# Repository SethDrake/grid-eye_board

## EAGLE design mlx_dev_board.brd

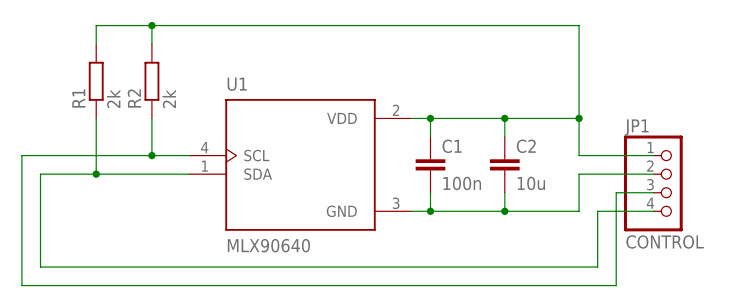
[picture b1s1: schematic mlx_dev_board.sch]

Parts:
C1: 100n; C0805
C2: 10u; C0805
JP1: CONTROL; 1X04
R1, R2: 2k; R0805
U1: MLX90640; TO292P945H1165-4

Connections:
GND: C1.2, C2.2, JP1.2, U1.3 (GND)
SCL: JP1.3, R2.1, U1.4 (SCL)
SDA: JP1.4, R1.1, U1.1 (SDA)
VDD: C1.1, C2.1, JP1.1, R1.2, R2.2, U1.2 (VDD)

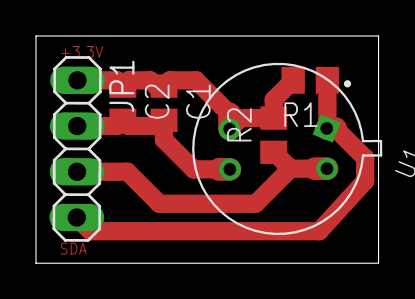
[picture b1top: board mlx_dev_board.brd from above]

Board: 2 copper layers, 19.0 x 12.6 mm, 6 parts (0 on the bottom side), 4 nets.

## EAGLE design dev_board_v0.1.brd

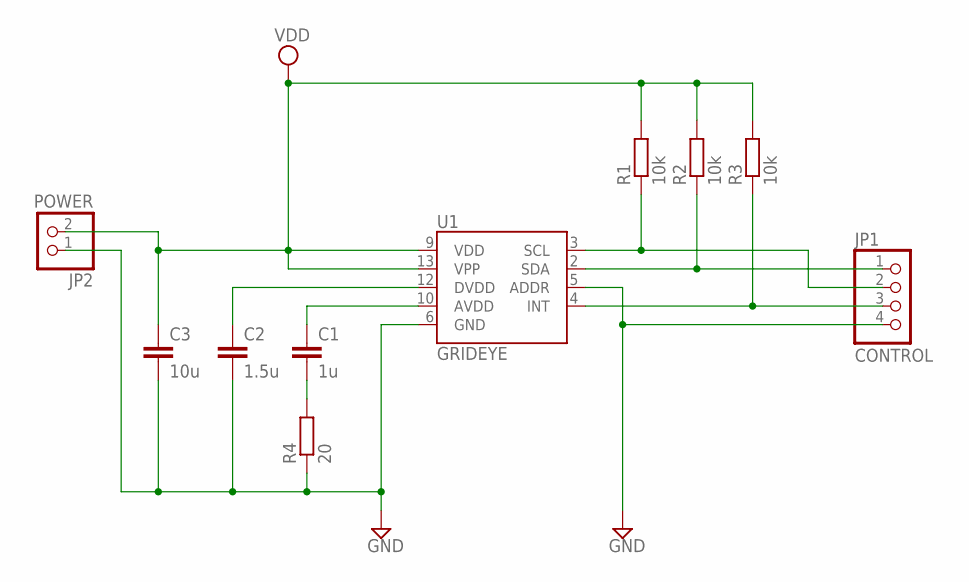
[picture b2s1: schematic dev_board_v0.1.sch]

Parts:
C1: 1u; C0805
C2: 1.5u; C0805
C3: 10u; C0805
JP1: CONTROL; 1X04
JP2: POWER; 1X02
R1, R2, R3: 10k; R0805
R4: 20; R0805
U1: GRIDEYE; GRIDEYE-AMG88

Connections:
AVDD: C1.1, U1.10 (AVDD)
DVDD: C2.1, U1.12 (DVDD)
GND: C2.2, C3.2, JP1.4, JP2.1, R4.1, U1.5 (ADDR), U1.6 (GND)
INT: JP1.3, R3.1, U1.4 (INT)
unnamed: C1.2, R4.2
SCL: JP1.2, R1.1, U1.3 (SCL)
SDA: JP1.1, R2.1, U1.2 (SDA)
VDD: C3.1, JP2.2, R1.2, R2.2, R3.2, U1.9 (VDD), U1.13 (VPP)

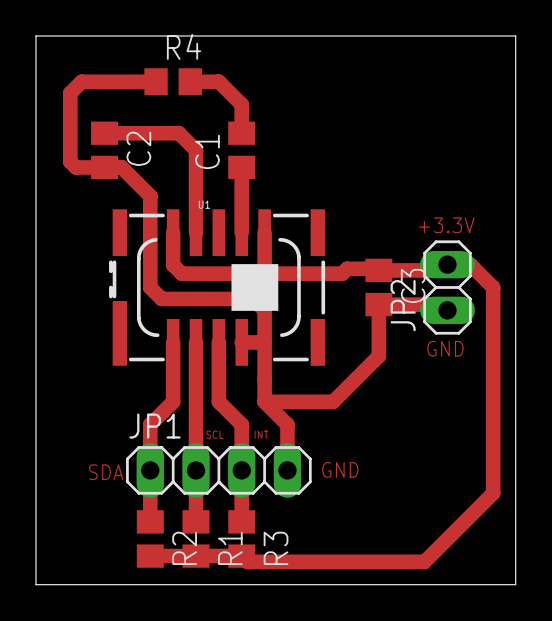
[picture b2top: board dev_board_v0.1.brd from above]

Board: 2 copper layers, 26.6 x 30.5 mm, 10 parts (0 on the bottom side), 8 nets.

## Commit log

2018-10-09 basic scheme v0.1
2018-10-09 board v0.1
2018-10-10 firmware for STM32F429-Discovery
2018-10-10 fw in progress
2018-10-14 fw in progress..
2018-10-15 fw in progress - text draw, visualization
2018-10-15 fw in progress - th visualization
2018-10-16 added DMA2D basic support
2018-10-17 fw in progress - th visualization - added bi-linear interpolation for color and temperature
2019-01-05 lcd in spi mode
2019-01-05 error handler, display output improved
2019-01-05 improvements, error handling
2019-01-08 ov7670 camera driver in progress
2019-01-12 dcmi in progress..
2019-01-13 working DCMI with ov7670
2019-01-20 dcmi working, thermal working dm2d blending performance is horrible
2020-11-18 updated vs & visualgdb
2022-01-09 port to mlx90640
2022-01-10 mlx90640 board
2022-01-10 pcb print layout
2022-01-11 improvements
2022-01-21 small improvements
